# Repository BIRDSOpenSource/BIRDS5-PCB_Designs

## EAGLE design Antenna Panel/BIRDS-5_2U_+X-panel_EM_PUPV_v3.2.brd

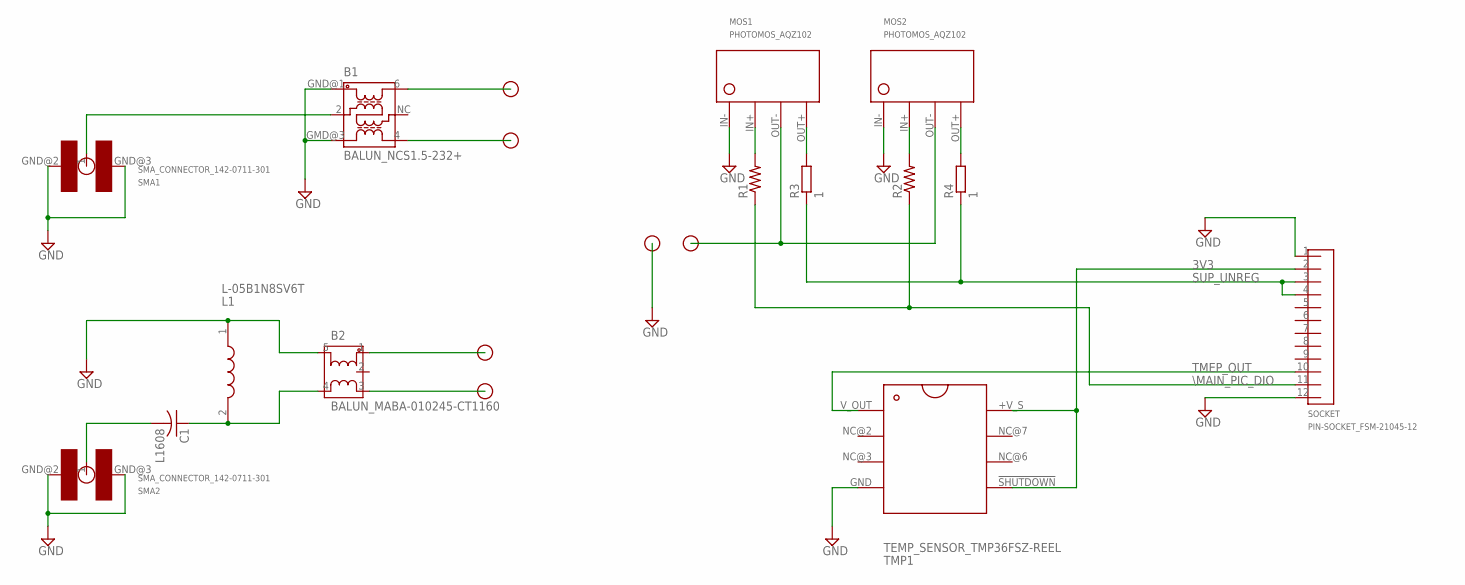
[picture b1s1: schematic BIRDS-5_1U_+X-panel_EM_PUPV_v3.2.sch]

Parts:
B1: BALUN_NCS1.5-232+; NCS1.5-232+
B2: BALUN_MABA-010245-CT1160; MABA-010245-CT1160
C1: L1608
FD1, FD2: FEED_POINT_HEAT_KNIFE
FP1_UHF, FP2_UHF, FP3, FP4: FEED_POINT
L1: L-05B1N8SV6T; INDC0603X33N
MOS1, MOS2: PHOTOMOS_AQZ102; AQZ102
R1, R2: R-US_R0402; R0402
R3, R4: 1; R1218
SMA1, SMA2: SMA_CONNECTOR_142-0711-301; 142-0711-301
SOCKET: PIN-SOCKET_FSM-21045-12
TMP1: TEMP_SENSOR_TMP36FSZ-REEL; TMP36FSZ-REEL

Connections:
3V3: SOCKET.2, TMP1.!SHUTDOWN!, TMP1.+V_S
GND: B1.GMD@3 (GND), B1.GND@1 (GND), B2.5, FD2.FP, L1.1, MOS1.IN-, MOS2.IN-, SMA1.GND@2 (GND), SMA1.GND@3 (GMD), SMA2.GND@2 (GND), SMA2.GND@3 (GMD), SOCKET.1, SOCKET.12, TMP1.GND
unnamed: MOS1.IN+, R1.2
unnamed: MOS2.IN+, R2.2
unnamed: MOS2.OUT+, R4.2
unnamed: MOS1.OUT+, R3.2
unnamed: FD1.FP, MOS1.OUT-, MOS2.OUT-
unnamed: B1.2, SMA1.1
unnamed: C1.2, SMA2.1
unnamed: B2.4, C1.1, L1.2
unnamed: B2.1, FP3.FP
unnamed: B2.3, FP4.FP
unnamed: B1.6, FP1_UHF.FP
unnamed: B1.4, FP2_UHF.FP
SUP_UNREG: R3.1, R4.1, SOCKET.3, SOCKET.4
TMEP_OUT: SOCKET.10, TMP1.V_OUT
\MAIN_PIC_DIO: R1.1, R2.1, SOCKET.11

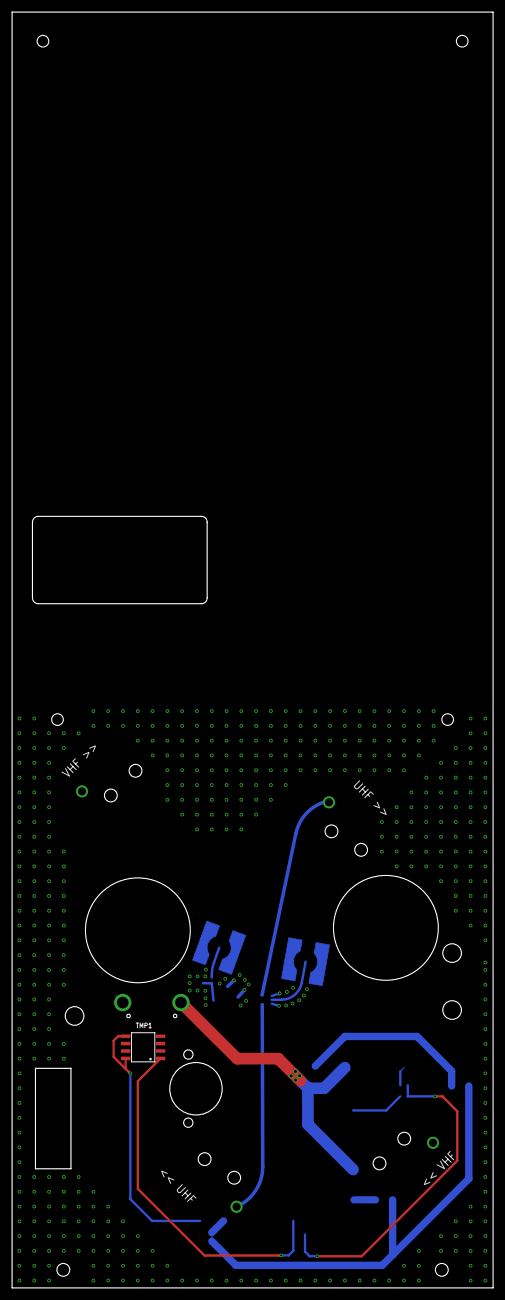
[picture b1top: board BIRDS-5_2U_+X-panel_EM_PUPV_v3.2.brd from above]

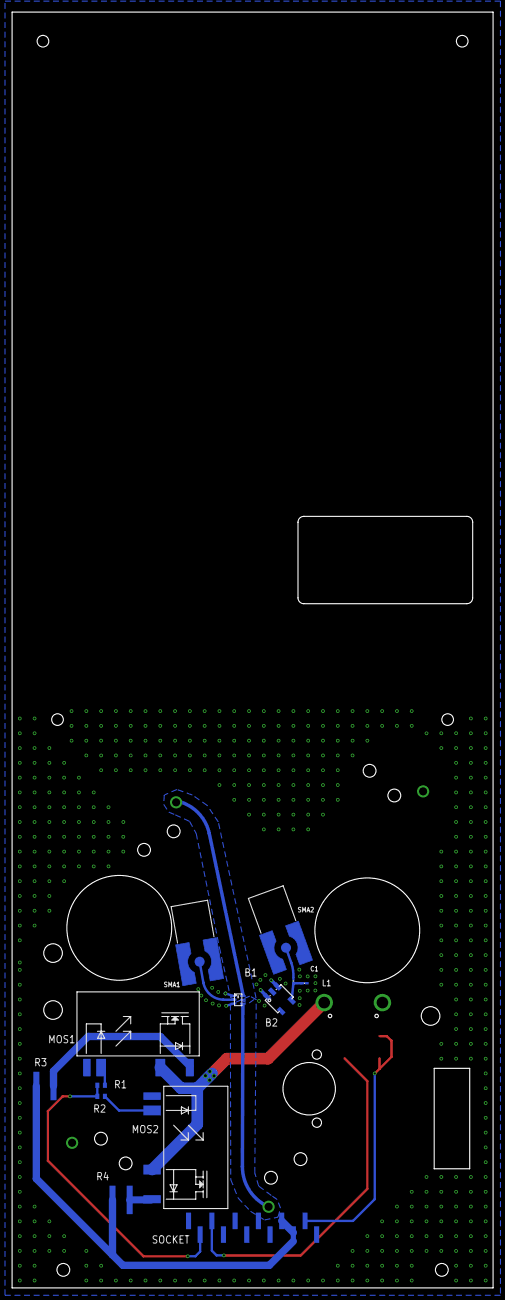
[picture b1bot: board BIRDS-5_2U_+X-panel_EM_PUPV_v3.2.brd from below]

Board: 4 copper layers, 82.6 x 219.1 mm, 20 parts (13 on the bottom side), 17 nets.

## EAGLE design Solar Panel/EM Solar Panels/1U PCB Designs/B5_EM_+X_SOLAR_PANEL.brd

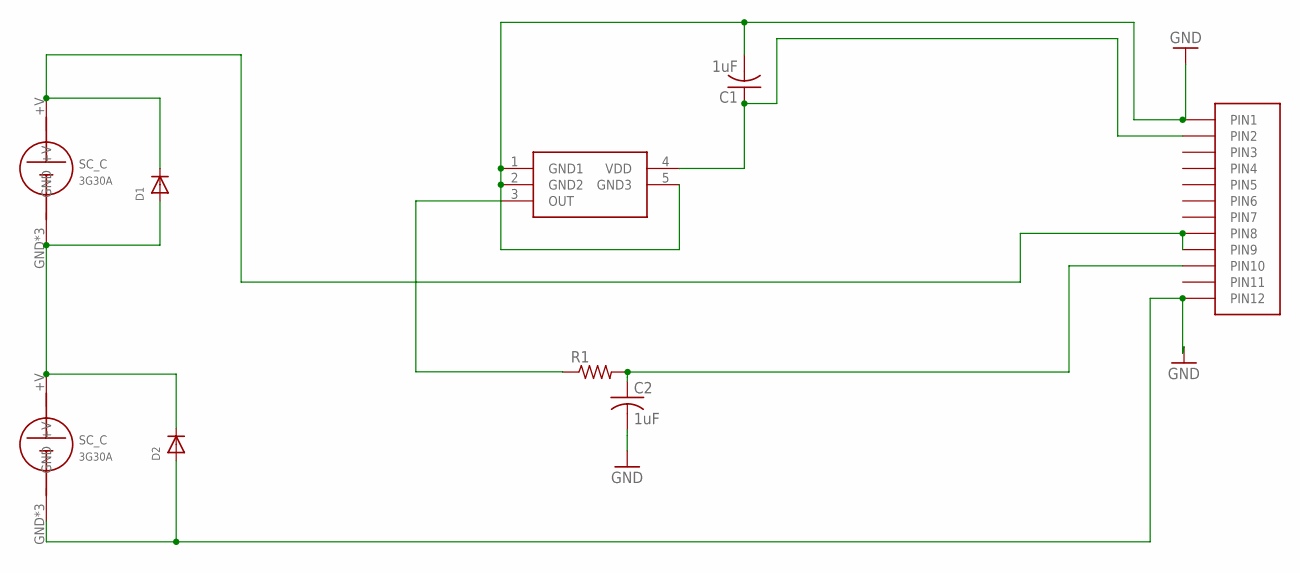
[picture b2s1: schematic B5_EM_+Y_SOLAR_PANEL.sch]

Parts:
C1, C2: 1uF; C0805
D1, D2: DIODE_SOD-123FL; SOD-123FL
R1: R-US_R0402; R0402
U$1: HEADER12PIN
U$3: LMT84DCKT; SOT65P210X110-5N
U$4, U$5: SC_C

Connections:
GND: C1.2, C2.2, D2.A, U$1.P1 (PIN1), U$1.P12 (PIN12), U$3.1 (GND1), U$3.2 (GND2), U$3.5 (GND3), U$4.GND, U$4.GND1 (GND), U$4.GND2 (GND)
unnamed: R1.1, U$3.3 (OUT)
unnamed: C2.1, R1.2, U$1.P10 (PIN10)
unnamed: D1.A, D2.C, U$4.+V, U$5.GND, U$5.GND1 (GND), U$5.GND2 (GND)
unnamed: D1.C, U$1.P8 (PIN8), U$1.P9 (PIN9), U$5.+V
unnamed: C1.1, U$1.P2 (PIN2), U$3.4 (VDD)

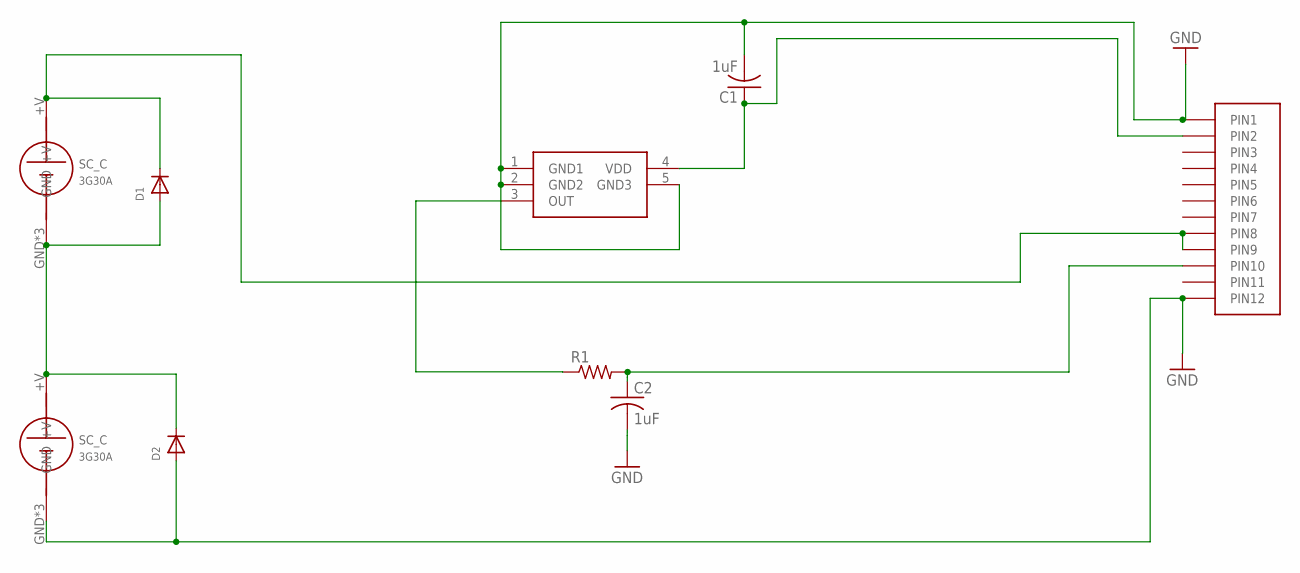
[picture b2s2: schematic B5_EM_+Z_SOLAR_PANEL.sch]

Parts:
C1, C2: 1uF; C0805
D1, D2: DIODE_SOD-123FL; SOD-123FL
R1: R-US_R0402; R0402
U$1: HEADER12PIN
U$3: LMT84DCKT; SOT65P210X110-5N
U$4, U$5: SC_C

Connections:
GND: C1.2, C2.2, D2.A, U$1.P1 (PIN1), U$1.P12 (PIN12), U$3.1 (GND1), U$3.2 (GND2), U$3.5 (GND3), U$4.GND, U$4.GND1 (GND), U$4.GND2 (GND)
unnamed: R1.1, U$3.3 (OUT)
unnamed: C2.1, R1.2, U$1.P10 (PIN10)
unnamed: D1.A, D2.C, U$4.+V, U$5.GND, U$5.GND1 (GND), U$5.GND2 (GND)
unnamed: D1.C, U$1.P8 (PIN8), U$1.P9 (PIN9), U$5.+V
unnamed: C1.1, U$1.P2 (PIN2), U$3.4 (VDD)

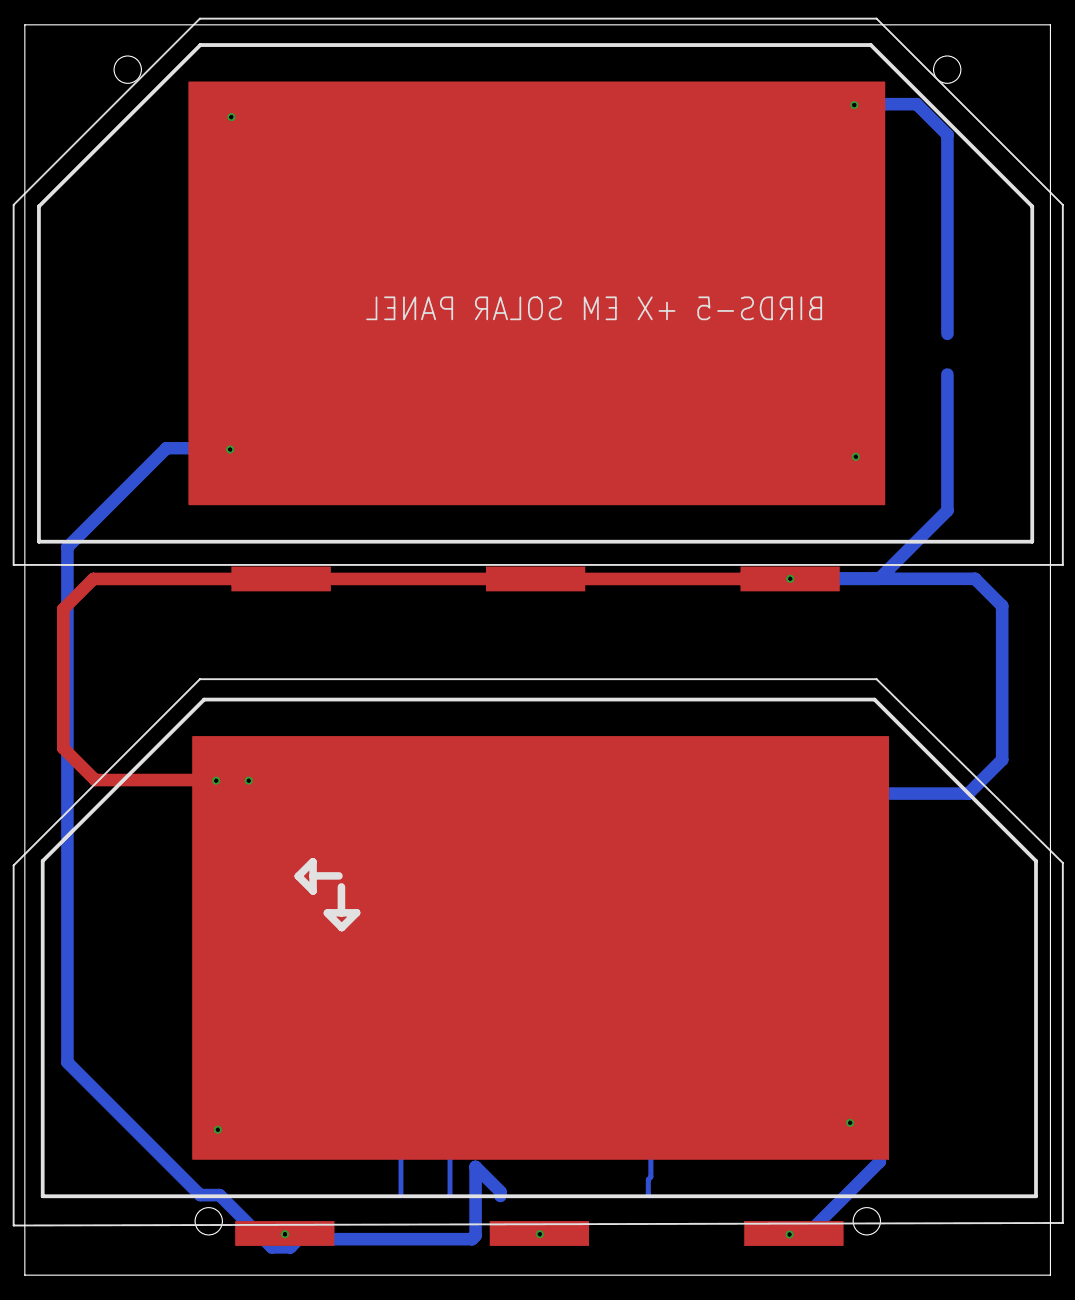
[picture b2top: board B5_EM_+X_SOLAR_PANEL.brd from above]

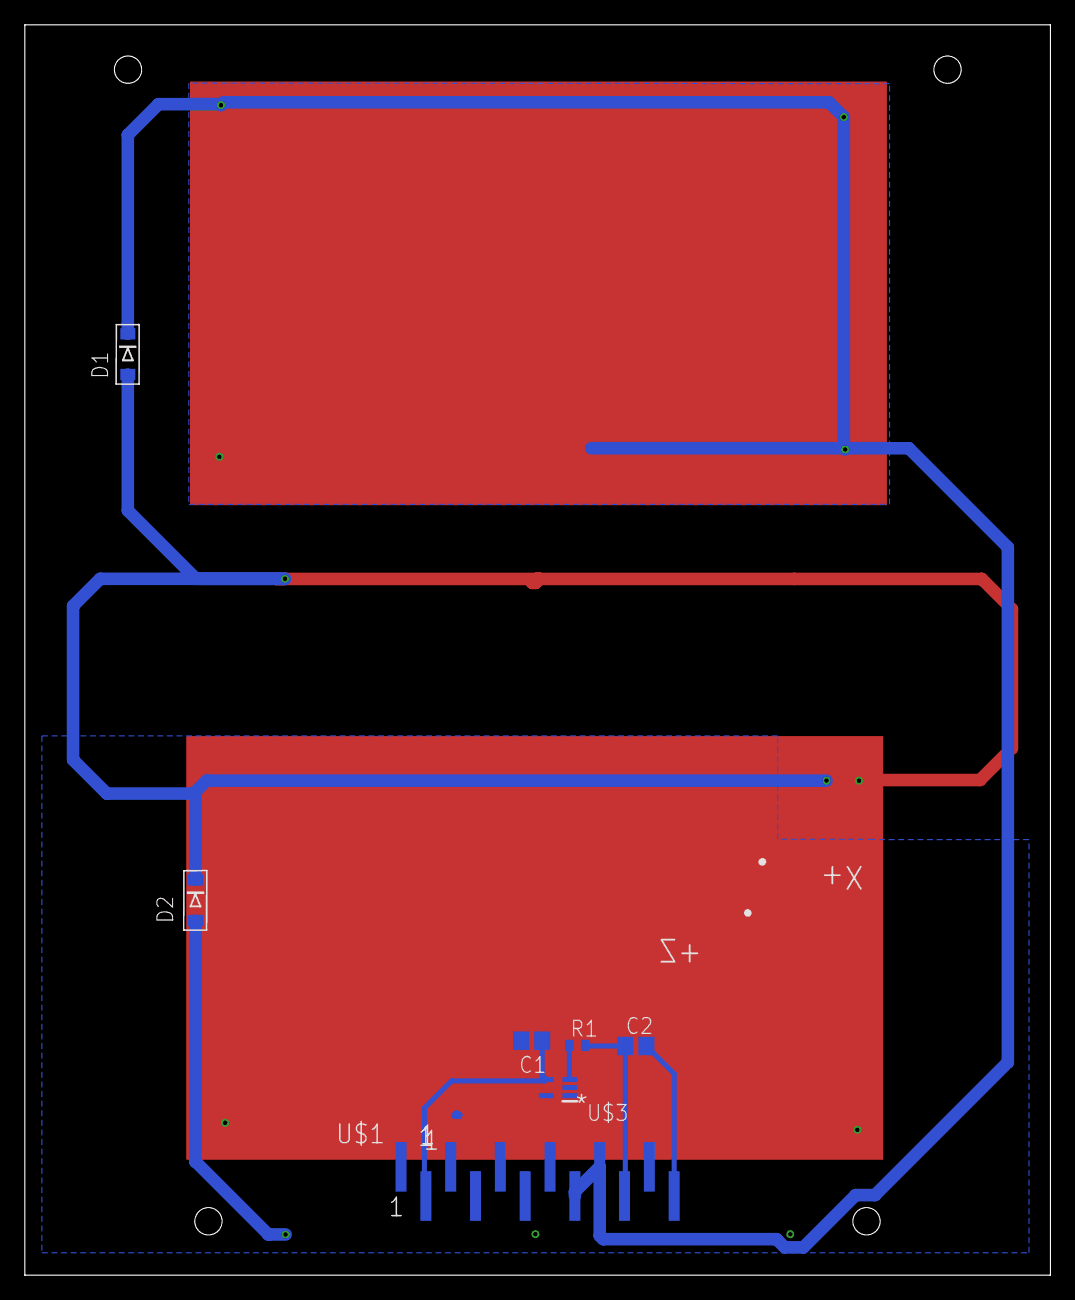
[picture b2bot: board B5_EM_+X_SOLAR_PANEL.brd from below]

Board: 2 copper layers, 82.6 x 100.7 mm, 9 parts (7 on the bottom side), 6 nets.

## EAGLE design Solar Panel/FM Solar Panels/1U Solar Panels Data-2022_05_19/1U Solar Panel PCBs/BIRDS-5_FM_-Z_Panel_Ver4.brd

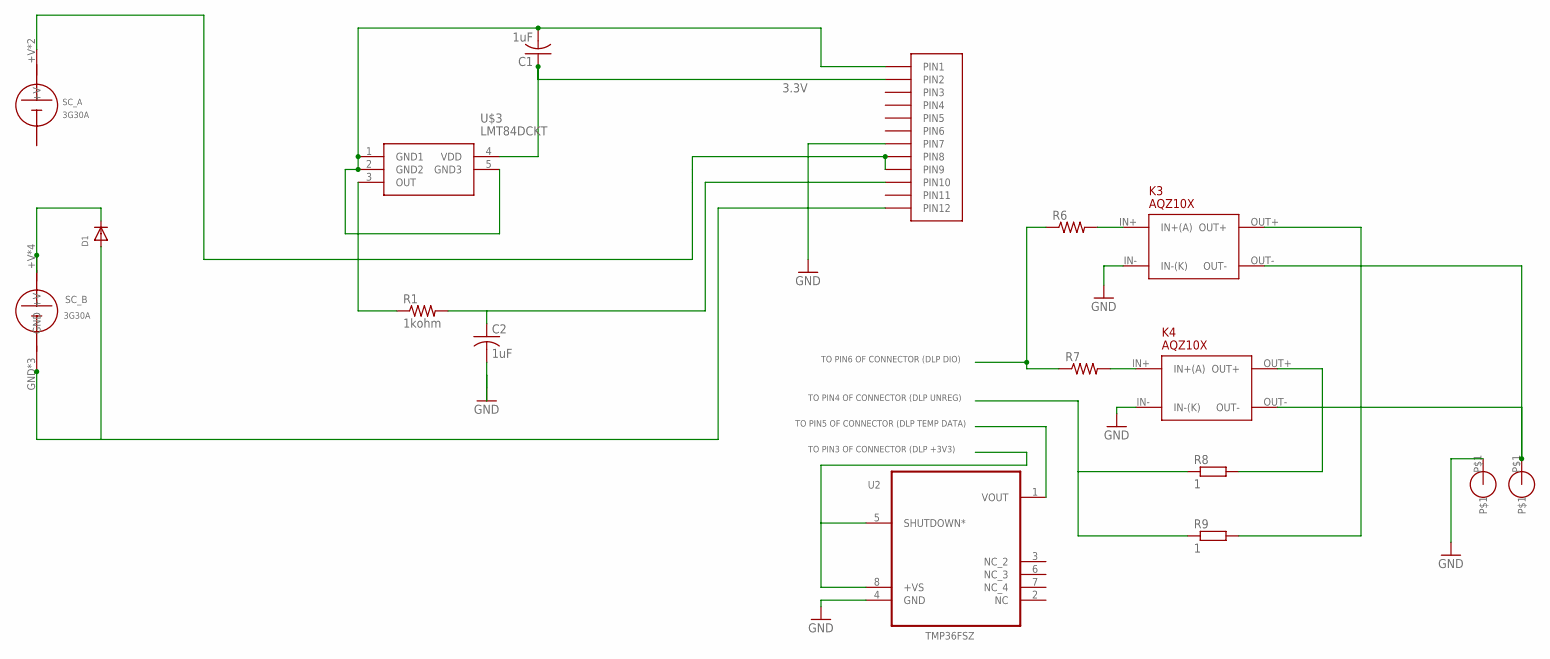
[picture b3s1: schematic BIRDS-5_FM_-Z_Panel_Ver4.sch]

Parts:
C1, C2: 1uF; C0805
D1: DIODE_SOD-123FL; SOD-123FL
GND9: NICR_HOLE
HOLE1: NICR_HOLE
K3, K4: AQZ10X
R1: 1kohm; R0402
R6, R7: R-US_R0402; R0402
R8, R9: 1; R1218
U2: TMP36FSZ; SOIC_N
U$1: HEADER12PIN
U$3: LMT84DCKT; SOT65P210X110-5N
U$4: SC_A
U$5: SC_B

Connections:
3.3V: U2.5 (SHUTDOWN*), U2.8 (+VS)
+V: U$1.P8 (PIN8), U$1.P9 (PIN9), U$4.+V, U$4.+V1
+VB: D1.C, U$5.+V, U$5.+V2 (+V), U$5.+V3 (+V), U$5.+V4 (+V)
DIO: R6.1, R7.1
GND: C1.2, C2.2, D1.A, GND9.P$1, K3.IN- (IN-(K)), K4.IN- (IN-(K)), U2.4 (GND), U$1.P1 (PIN1), U$1.P7 (PIN7), U$1.P12 (PIN12), U$3.1 (GND1), U$3.2 (GND2), U$3.5 (GND3), U$5.GND, U$5.GND1 (GND), U$5.GND2 (GND)
unnamed: C2.1, R1.2, U$1.P10 (PIN10)
unnamed: C1.1, U$1.P2 (PIN2), U$3.4 (VDD)
unnamed: K3.IN+ (IN+(A)), R6.2
unnamed: K4.IN+ (IN+(A)), R7.2
unnamed: K3.OUT+, R9.2
unnamed: K4.OUT+, R8.2
unnamed: R1.1, U$3.3 (OUT)
unnamed: HOLE1.P$1, K3.OUT-, K4.OUT-
UNREG: R8.1, R9.1

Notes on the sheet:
TO PIN6 OF CONNECTOR (DLP DIO)
TO PIN4 OF CONNECTOR (DLP UNREG)
TO PIN5 OF CONNECTOR (DLP TEMP DATA)
TO PIN3 OF CONNECTOR (DLP +3V3)

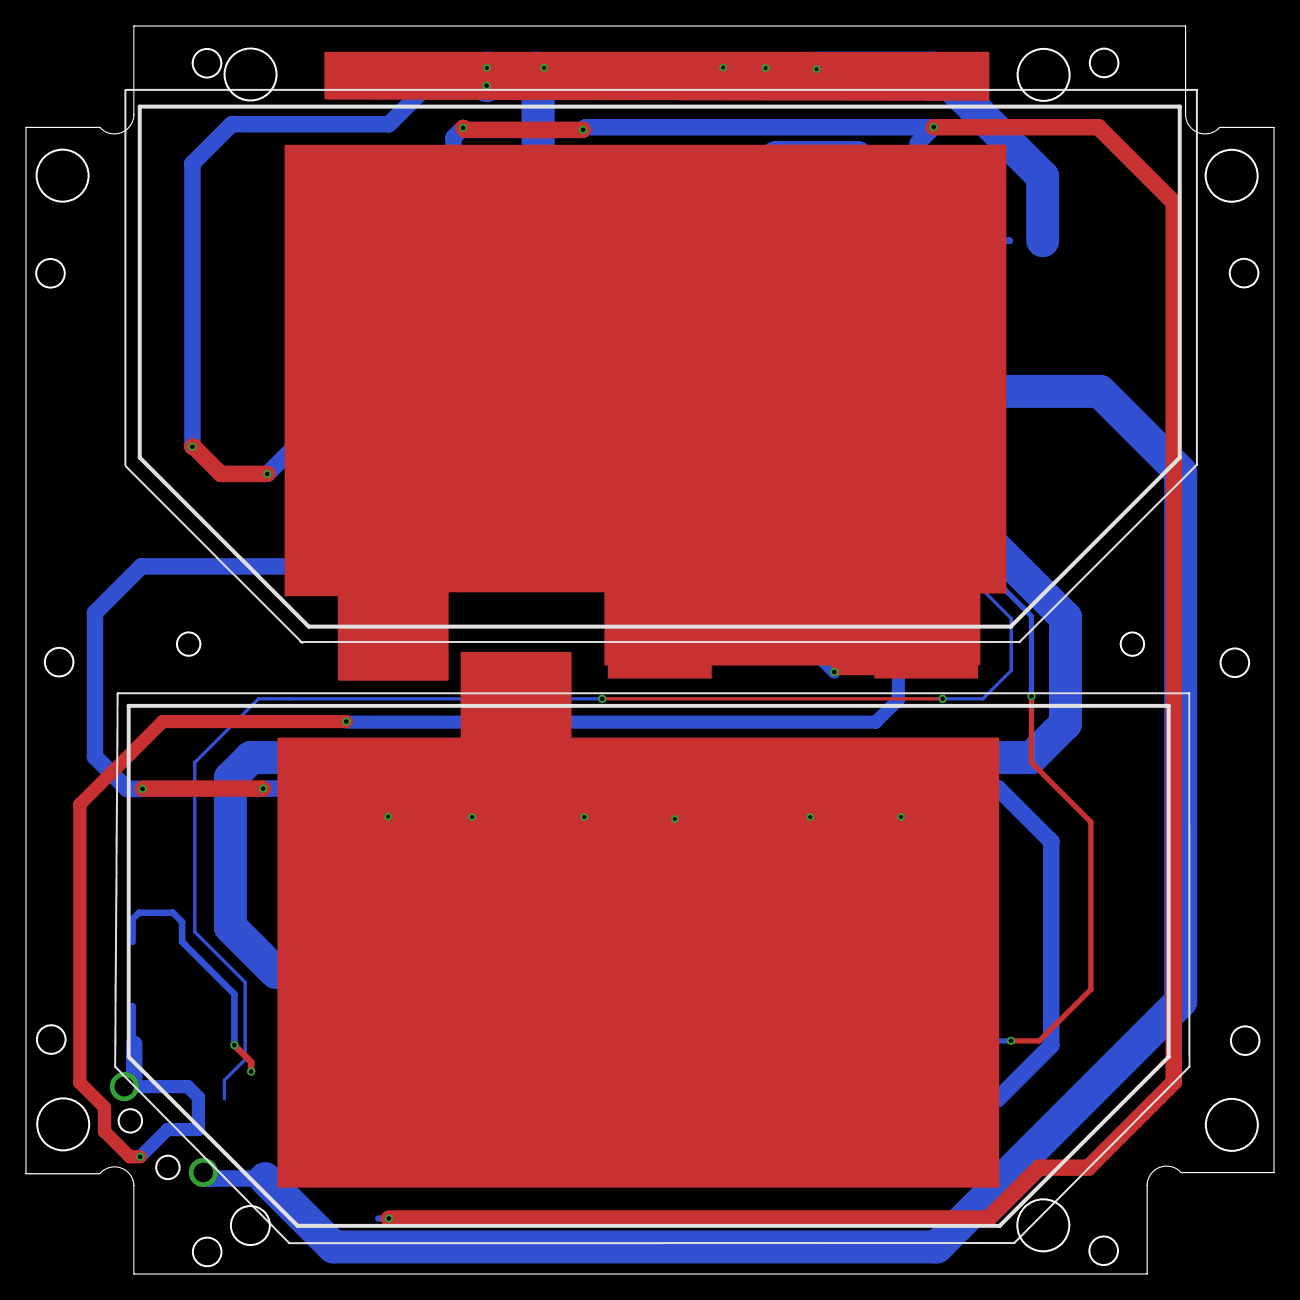
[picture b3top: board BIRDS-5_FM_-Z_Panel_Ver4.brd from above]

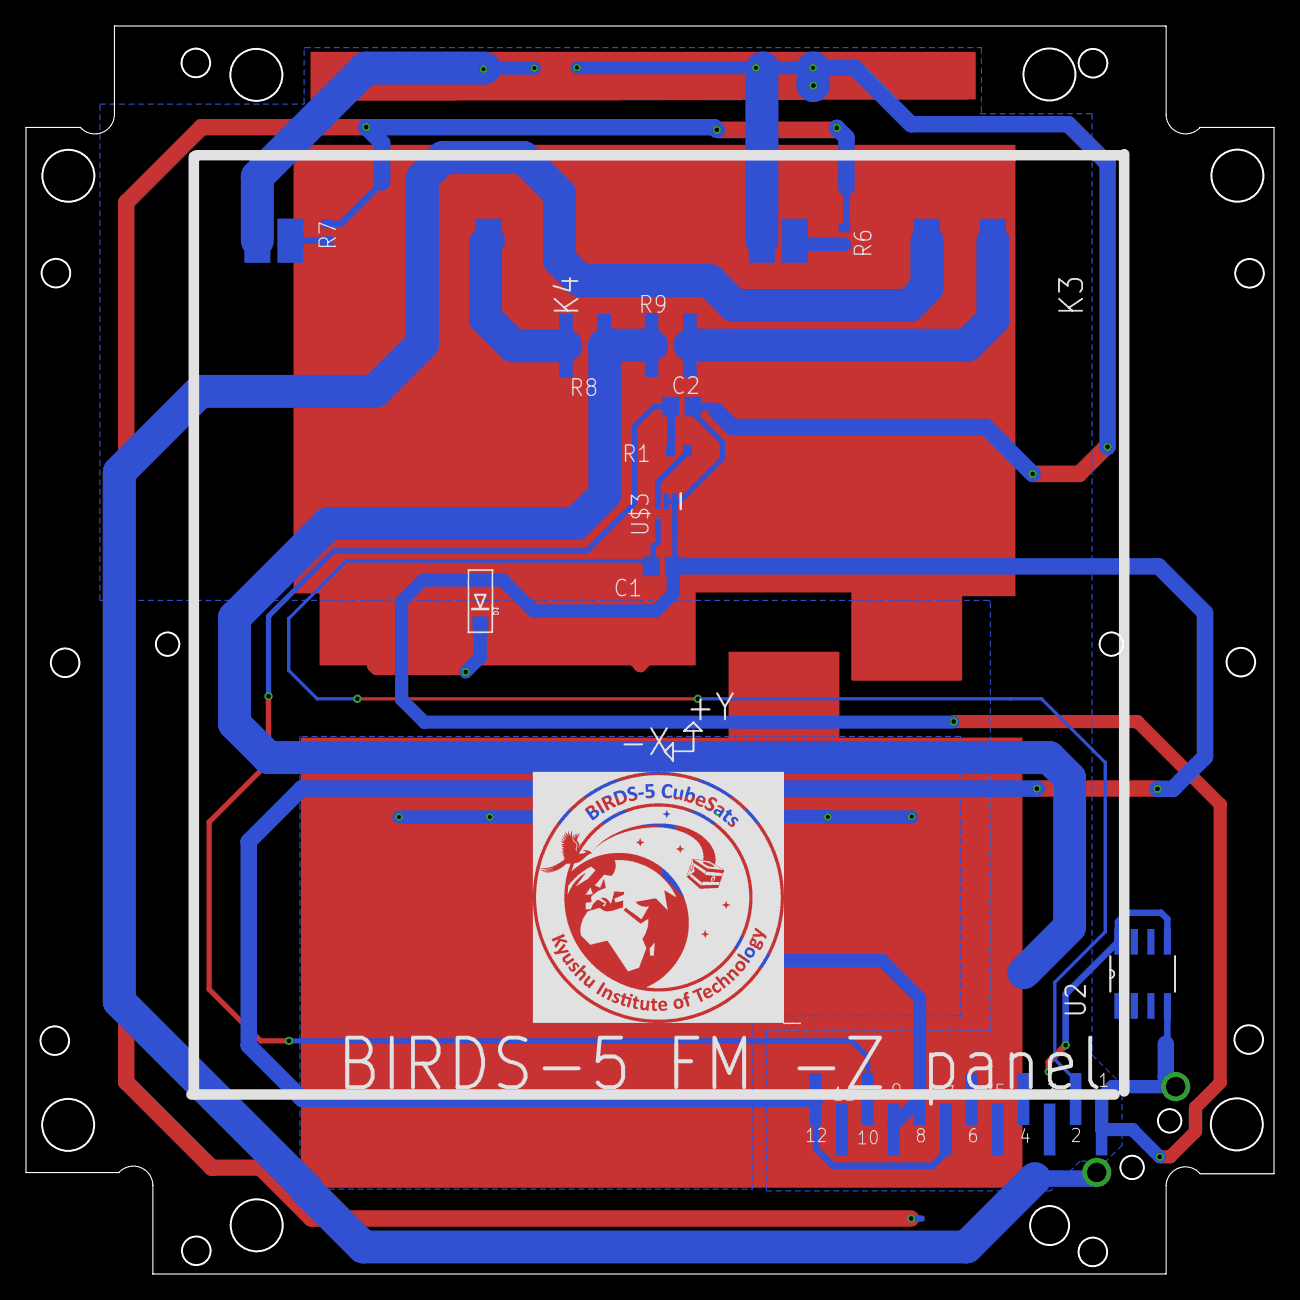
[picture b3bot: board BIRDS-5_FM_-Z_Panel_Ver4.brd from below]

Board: 2 copper layers, 96.0 x 96.0 mm, 17 parts (12 on the bottom side), 14 nets.
